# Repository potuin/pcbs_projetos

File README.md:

# 🔌 Portfólio de Design de PCBs & Eletrónica — Marco Silva

Bem-vindo(a) ao meu repositório de projetos de hardware! 

Este espaço é dedicado à documentação e partilha dos meus projetos de **Placas de Circuito Impresso (PCBs)** e desenvolvimento de sistemas embebidos, abrangendo todo o fluxo de engenharia EDA: desde a conceção do esquemático elétrico, seleção de componentes, cálculo e roteamento de pistas, até à validação por DRC e geração dos ficheiros industriais de fabrico.

---

## 🛠️ Ferramentas & Metodologia de Trabalho

* **Software EDA:** KiCad
* **Dimensionamento Técnico:** Norma **IPC-2221** (Cálculos de largura de pistas, capacidade de corrente e gestão térmica)
* **Regras de Desenho:** DFM (*Design for Manufacturability*) com validação estrita por ERC/DRC (Zero Erros / Zero Desconexões)
* **Documentação & Produção:** Emissão de relatórios técnicos e geração de ficheiros standard industriais (Gerber RS-274X / Excellon Drill)

---

## 📂 Organização do Repositório

Os ficheiros e documentação deste projeto encontram-se distribuídos pelas seguintes pastas:

* 📁 **[`/Hardware`](./Hardware)** — Ficheiros de projeto e esquemático elétrico do KiCad (`.kicad_pcb`, `.kicad_sch`).
* 📁 **[`/gerbers`](./gerbers)** — Pacote compactado (`.zip`) com os ficheiros de fabrico Gerber e Drill prontos para produção.
* 📁 **[`/Docs`](./Docs)** — Relatório técnico de engenharia completo em formato PDF.

---

## 📬 Contacto & Redes
* **GitHub:** [@potuin](https://github.com/potuin)
* **LinkedIn:** (https://www.linkedin.com/in/marco-silva-22b086384/)

---
*Desenvolvido por Marco Silva — Projetos de Hardware & Engenharia EDA.*

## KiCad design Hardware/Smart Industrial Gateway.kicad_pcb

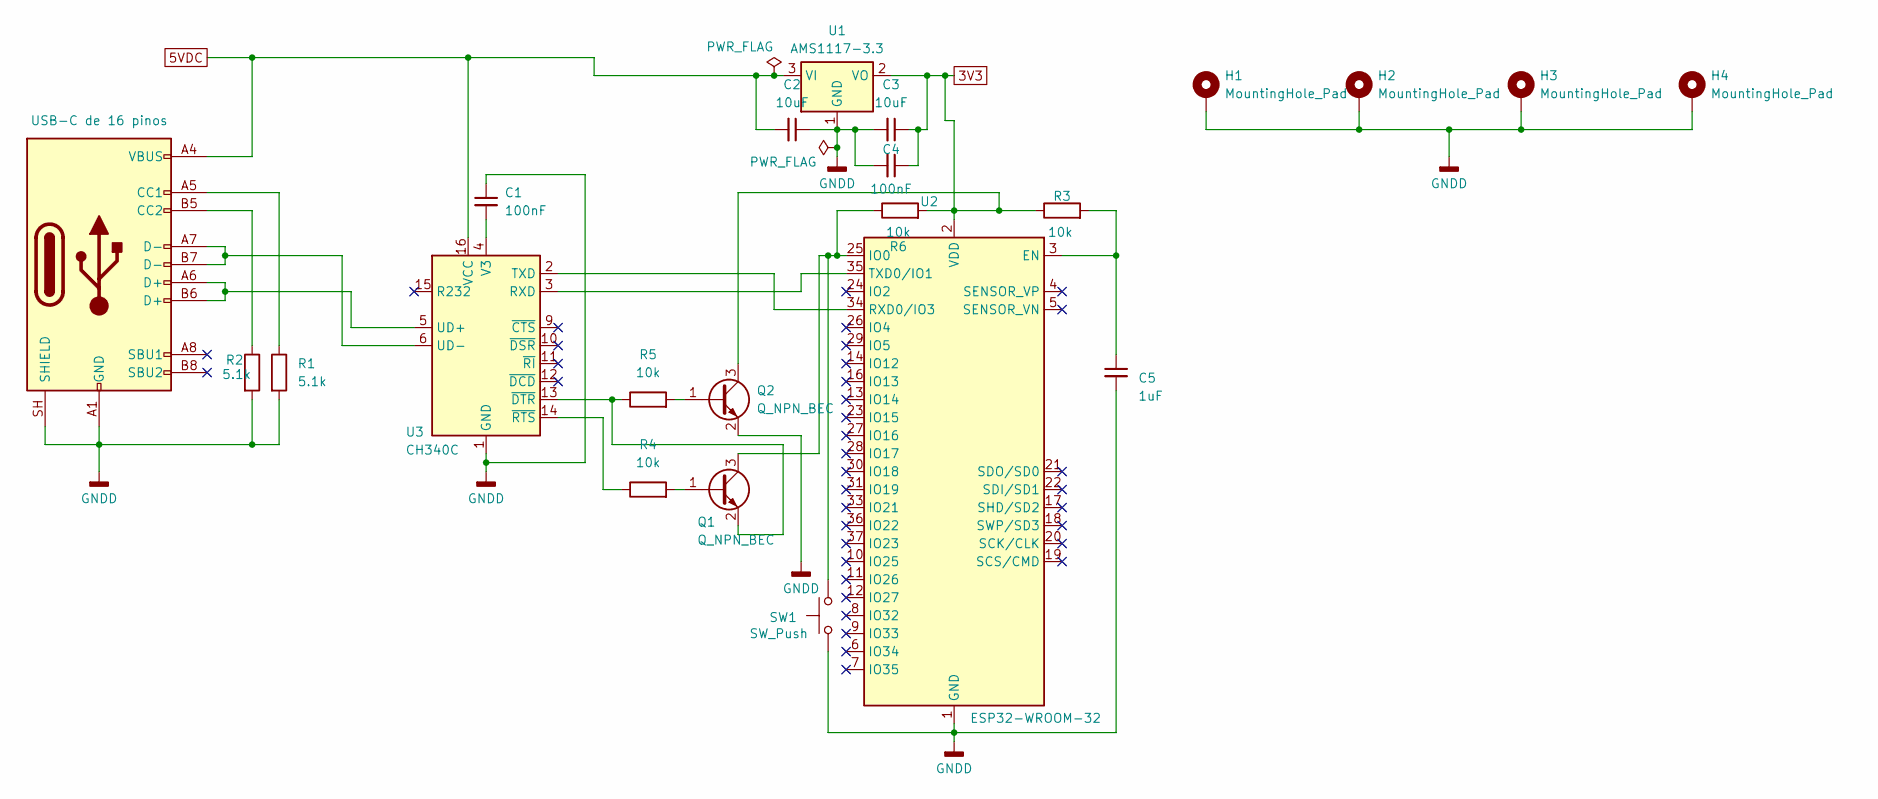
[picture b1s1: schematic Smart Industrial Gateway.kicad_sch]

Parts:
C1, C4: 100nF; C_0805_2012Metric
C2, C3: 10uF; C_0805_2012Metric
C5: 1uF; C_0805_2012Metric
H1, H2, H3, H4: MountingHole_Pad; MountingHole_3.2mm_M3_Pad
J1: USB-C de 16 pinos; USB_C_Receptacle_XKB_U262-16XN-4BVC11
Q1, Q2: Q_NPN_BEC; SOT-23
R1, R2: 5.1k; R_0805_2012Metric
R3, R4, R5, R6: 10k; R_0805_2012Metric
SW1: SW_Push; SW_PUSH_6mm
U1: AMS1117-3.3; SOT-223-3_TabPin2
U2: ESP32-WROOM-32
U3: CH340C; SOIC-16_3.9x9.9mm_P1.27mm

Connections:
3V3: C3.1, C4.1, Q2.3 (C), R3.1, R6.2, U1.2 (VO), U2.2 (VDD)
5VDC: C2.2, J1.A4 (VBUS), J1.A9 (VBUS), J1.B4 (VBUS), J1.B9 (VBUS), U1.3 (VI), U3.16 (VCC)
GNDD: C1.1, C2.1, C3.2, C4.2, C5.2, H1.1 (1_1), H2.1 (1_1), H3.1 (1_1), H4.1 (1_1), J1.A1 (GND), J1.A12 (GND), J1.B1 (GND), J1.B12 (GND), J1.SH (SHIELD), Q2.2 (E), R1.2, R2.2, SW1.1, U1.1 (GND), U2.1 (GND), U2.15 (GND), U2.38 (GND), U2.39 (GND), U3.1 (GND)
unnamed: J1.A5 (CC1), R1.1
unnamed: J1.B5 (CC2), R2.1
unnamed: Q1.1 (B), R4.2
unnamed: Q1.3 (C), R6.1, SW1.2, U2.25 (IO0)
unnamed: Q1.2 (E), R5.1, U3.13 (~DTR)
unnamed: Q2.1 (B), R5.2
unnamed: C5.1, R3.2, U2.3 (EN)
unnamed: U2.34 (RXD0/IO3), U3.2 (TXD)
unnamed: U2.35 (TXD0/IO1), U3.3 (RXD)
unnamed: J1.A6 (D+), J1.B6 (D+), U3.5 (UD+)
unnamed: J1.A7 (D-), J1.B7 (D-), U3.6 (UD-)
unnamed: C1.2, U3.4 (V3)
unnamed: R4.1, U3.14 (~RTS)

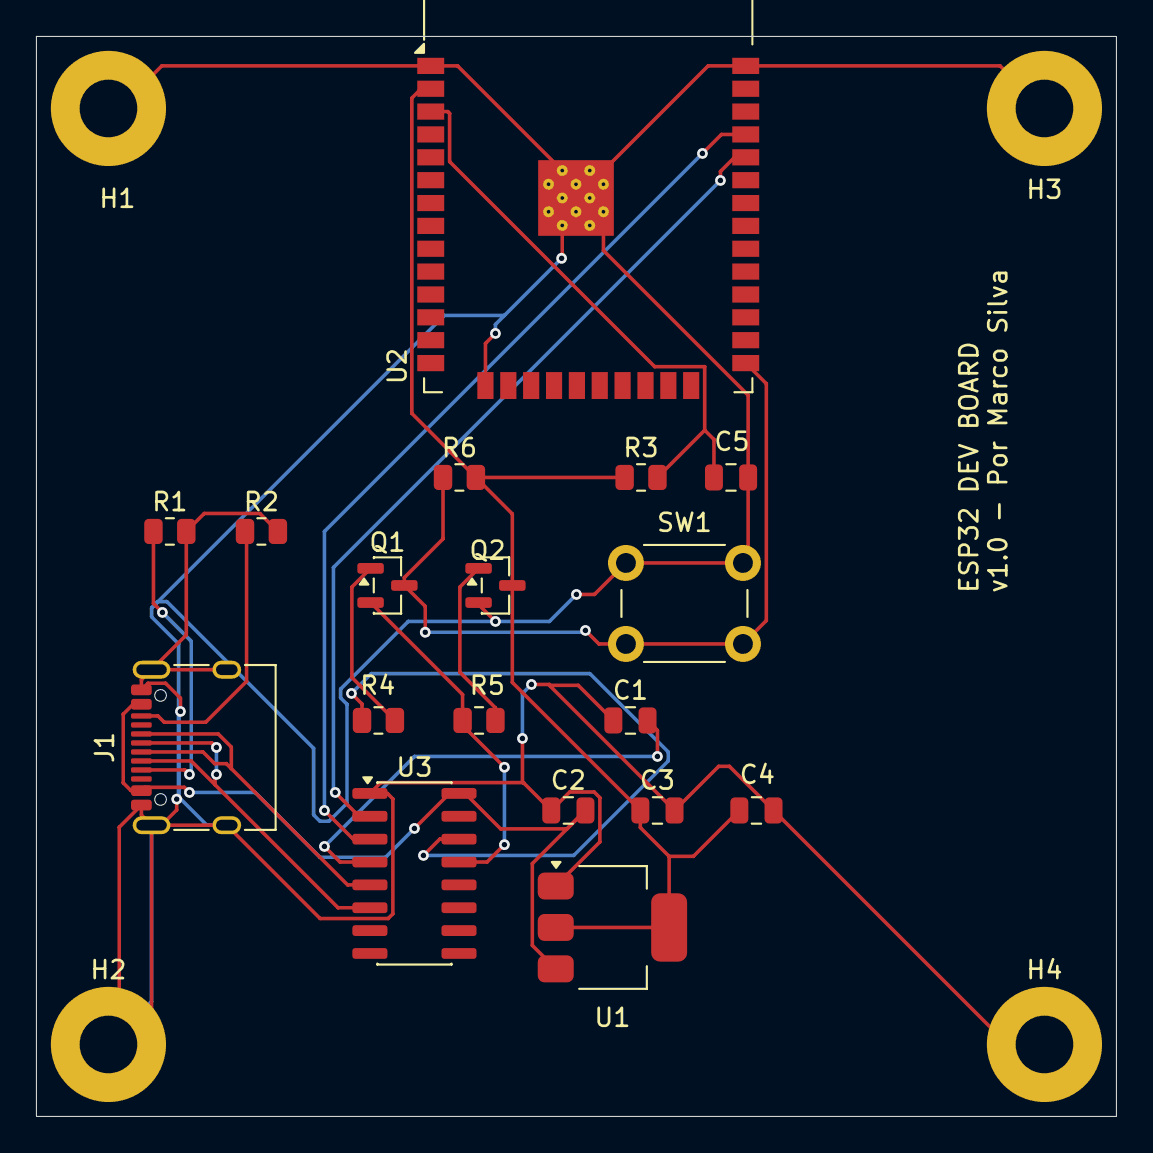
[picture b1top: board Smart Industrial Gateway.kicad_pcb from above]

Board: 2 copper layers, 60.0 x 60.0 mm, 22 parts (0 on the bottom side), 16 nets.
